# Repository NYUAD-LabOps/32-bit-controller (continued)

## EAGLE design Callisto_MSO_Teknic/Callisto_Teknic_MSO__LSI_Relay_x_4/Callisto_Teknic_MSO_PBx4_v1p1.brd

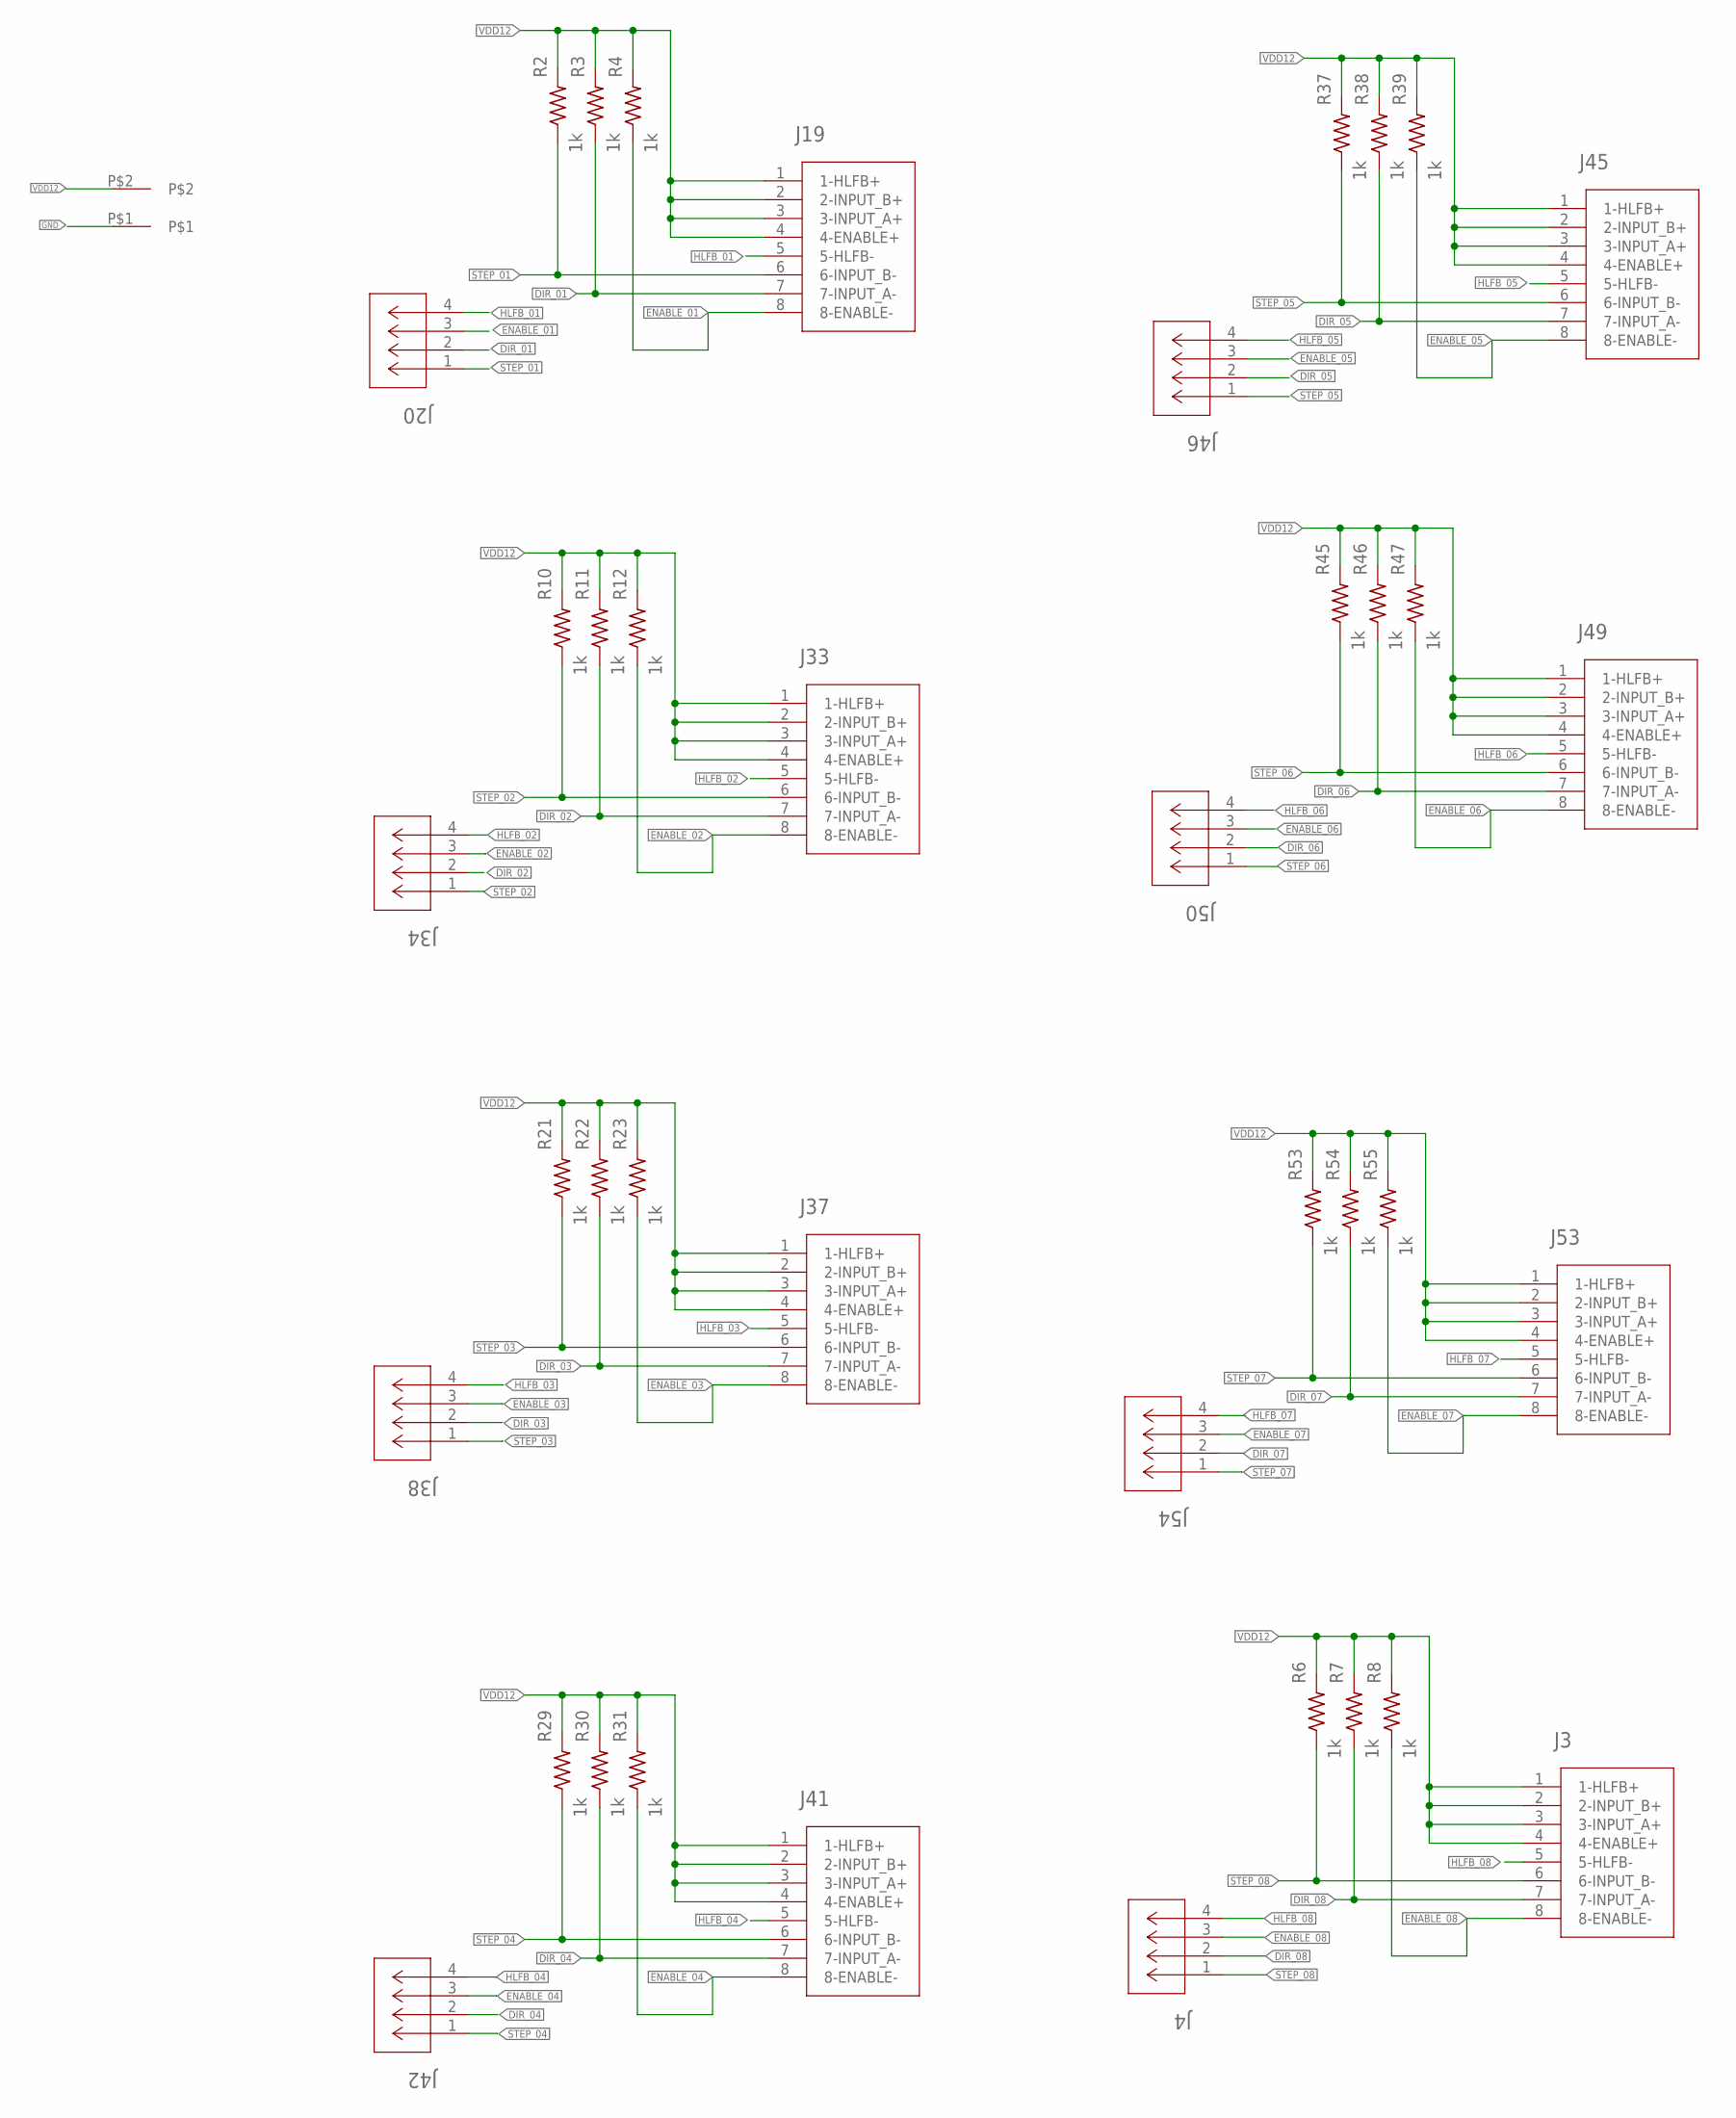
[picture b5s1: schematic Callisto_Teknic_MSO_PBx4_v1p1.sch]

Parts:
J2: 2-pos; 2_3.81MM_PITCH
J3, J19, J33, J37, J41, J45, J49, J53: TEKNIC_8PIN_MOTOR; CON_39281083
J4, J20, J34, J38, J42, J46, J50, J54: CONN_530470410_PICOBLADE_X_4; CON_530470410_MOL
R2, R3, R4, R6, R7, R8, R10, R11, R12, R21, R22, R23, R29, R30, R31, R37, R38, R39, R45, R46, R47, R53, R54, R55: 1k; 0805

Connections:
DIR_01: J19.7 (7-INPUT_A-), J20.2, R3.1
DIR_02: J33.7 (7-INPUT_A-), J34.2, R11.1
DIR_03: J37.7 (7-INPUT_A-), J38.2, R22.1
DIR_04: J41.7 (7-INPUT_A-), J42.2, R30.1
DIR_05: J45.7 (7-INPUT_A-), J46.2, R38.1
DIR_06: J49.7 (7-INPUT_A-), J50.2, R46.1
DIR_07: J53.7 (7-INPUT_A-), J54.2, R54.1
DIR_08: J3.7 (7-INPUT_A-), J4.2, R7.1
ENABLE_01: J19.8 (8-ENABLE-), J20.3, R4.1
ENABLE_02: J33.8 (8-ENABLE-), J34.3, R12.1
ENABLE_03: J37.8 (8-ENABLE-), J38.3, R23.1
ENABLE_04: J41.8 (8-ENABLE-), J42.3, R31.1
ENABLE_05: J45.8 (8-ENABLE-), J46.3, R39.1
ENABLE_06: J49.8 (8-ENABLE-), J50.3, R47.1
ENABLE_07: J53.8 (8-ENABLE-), J54.3, R55.1
ENABLE_08: J3.8 (8-ENABLE-), J4.3, R8.1
GND: J2.P$1
HLFB_01: J19.5 (5-HLFB-), J20.4
HLFB_02: J33.5 (5-HLFB-), J34.4
HLFB_03: J37.5 (5-HLFB-), J38.4
HLFB_04: J41.5 (5-HLFB-), J42.4
HLFB_05: J45.5 (5-HLFB-), J46.4
HLFB_06: J49.5 (5-HLFB-), J50.4
HLFB_07: J53.5 (5-HLFB-), J54.4
HLFB_08: J3.5 (5-HLFB-), J4.4
STEP_01: J19.6 (6-INPUT_B-), J20.1, R2.1
STEP_02: J33.6 (6-INPUT_B-), J34.1, R10.1
STEP_03: J37.6 (6-INPUT_B-), J38.1, R21.1
STEP_04: J41.6 (6-INPUT_B-), J42.1, R29.1
STEP_05: J45.6 (6-INPUT_B-), J46.1, R37.1
STEP_06: J49.6 (6-INPUT_B-), J50.1, R45.1
STEP_07: J53.6 (6-INPUT_B-), J54.1, R53.1
STEP_08: J3.6 (6-INPUT_B-), J4.1, R6.1
VDD12: J2.P$2, J3.1 (1-HLFB+), J3.2 (2-INPUT_B+), J3.3 (3-INPUT_A+), J3.4 (4-ENABLE+), J19.1 (1-HLFB+), J19.2 (2-INPUT_B+), J19.3 (3-INPUT_A+), J19.4 (4-ENABLE+), J33.1 (1-HLFB+), J33.2 (2-INPUT_B+), J33.3 (3-INPUT_A+), J33.4 (4-ENABLE+), J37.1 (1-HLFB+), J37.2 (2-INPUT_B+), J37.3 (3-INPUT_A+), J37.4 (4-ENABLE+), J41.1 (1-HLFB+), J41.2 (2-INPUT_B+), J41.3 (3-INPUT_A+), J41.4 (4-ENABLE+), J45.1 (1-HLFB+), J45.2 (2-INPUT_B+), J45.3 (3-INPUT_A+), J45.4 (4-ENABLE+), J49.1 (1-HLFB+), J49.2 (2-INPUT_B+), J49.3 (3-INPUT_A+), J49.4 (4-ENABLE+), J53.1 (1-HLFB+), J53.2 (2-INPUT_B+), J53.3 (3-INPUT_A+), J53.4 (4-ENABLE+), R2.2, R3.2, R4.2, R6.2, R7.2, R8.2, R10.2, R11.2, R12.2, R21.2, R22.2, R23.2, R29.2, R30.2, R31.2, R37.2, R38.2, R39.2, R45.2, R46.2, R47.2, R53.2, R54.2, R55.2

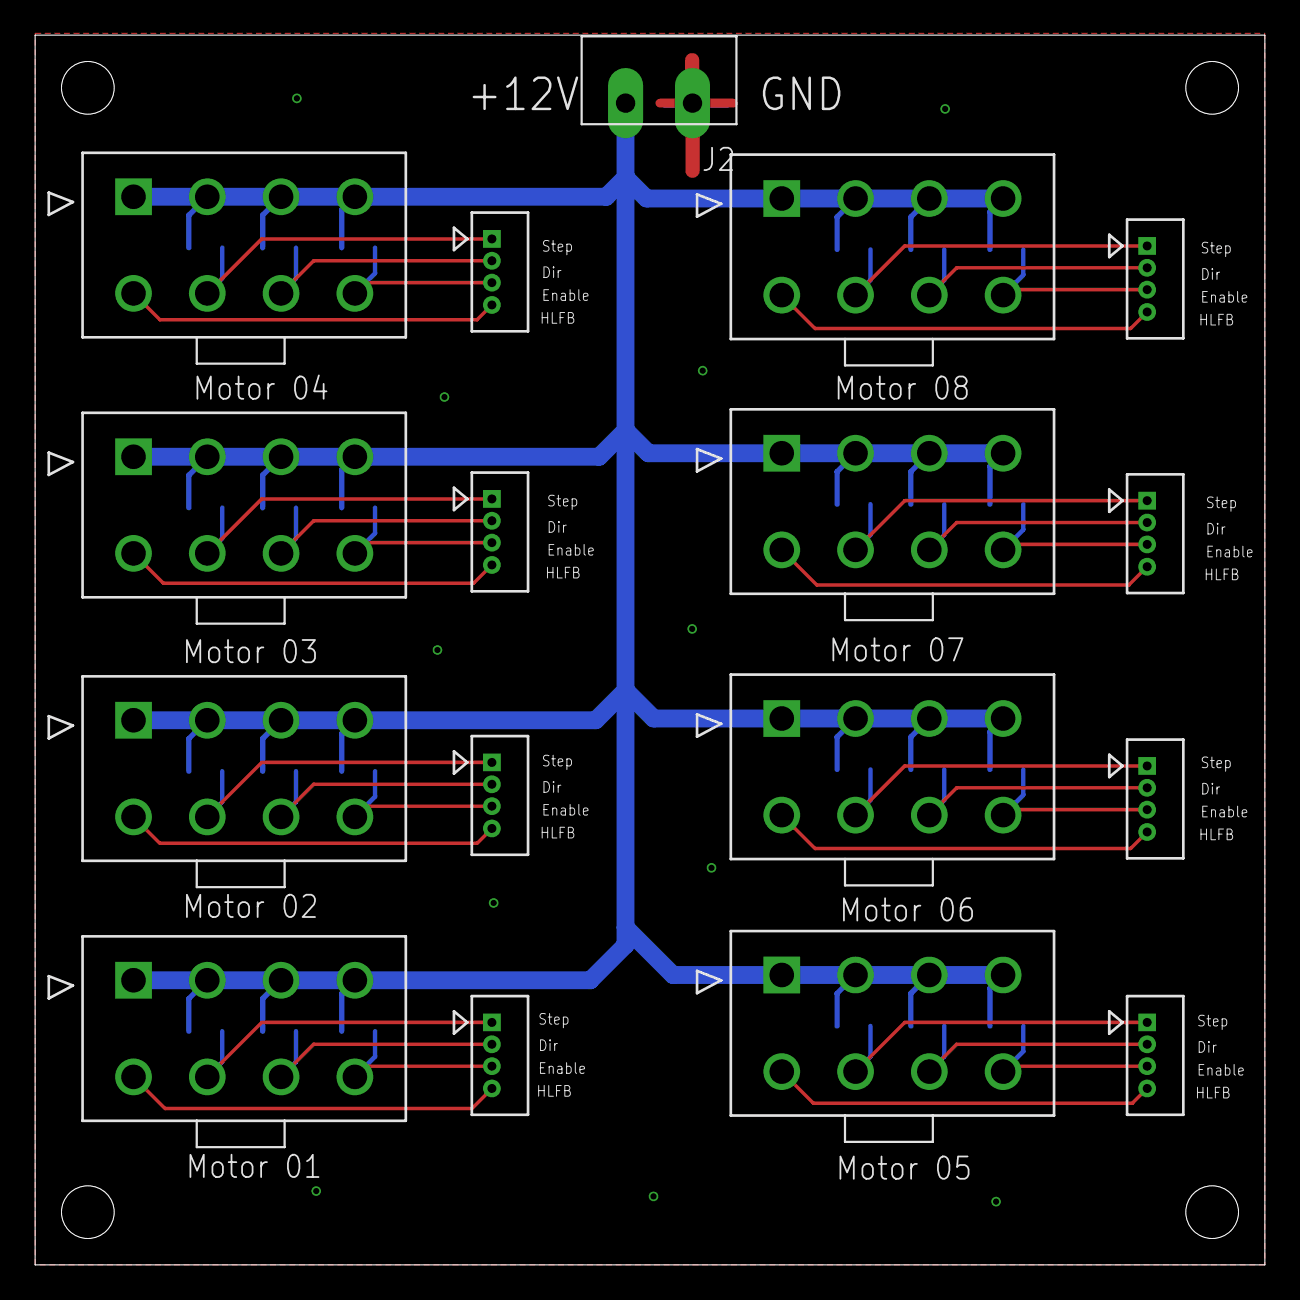
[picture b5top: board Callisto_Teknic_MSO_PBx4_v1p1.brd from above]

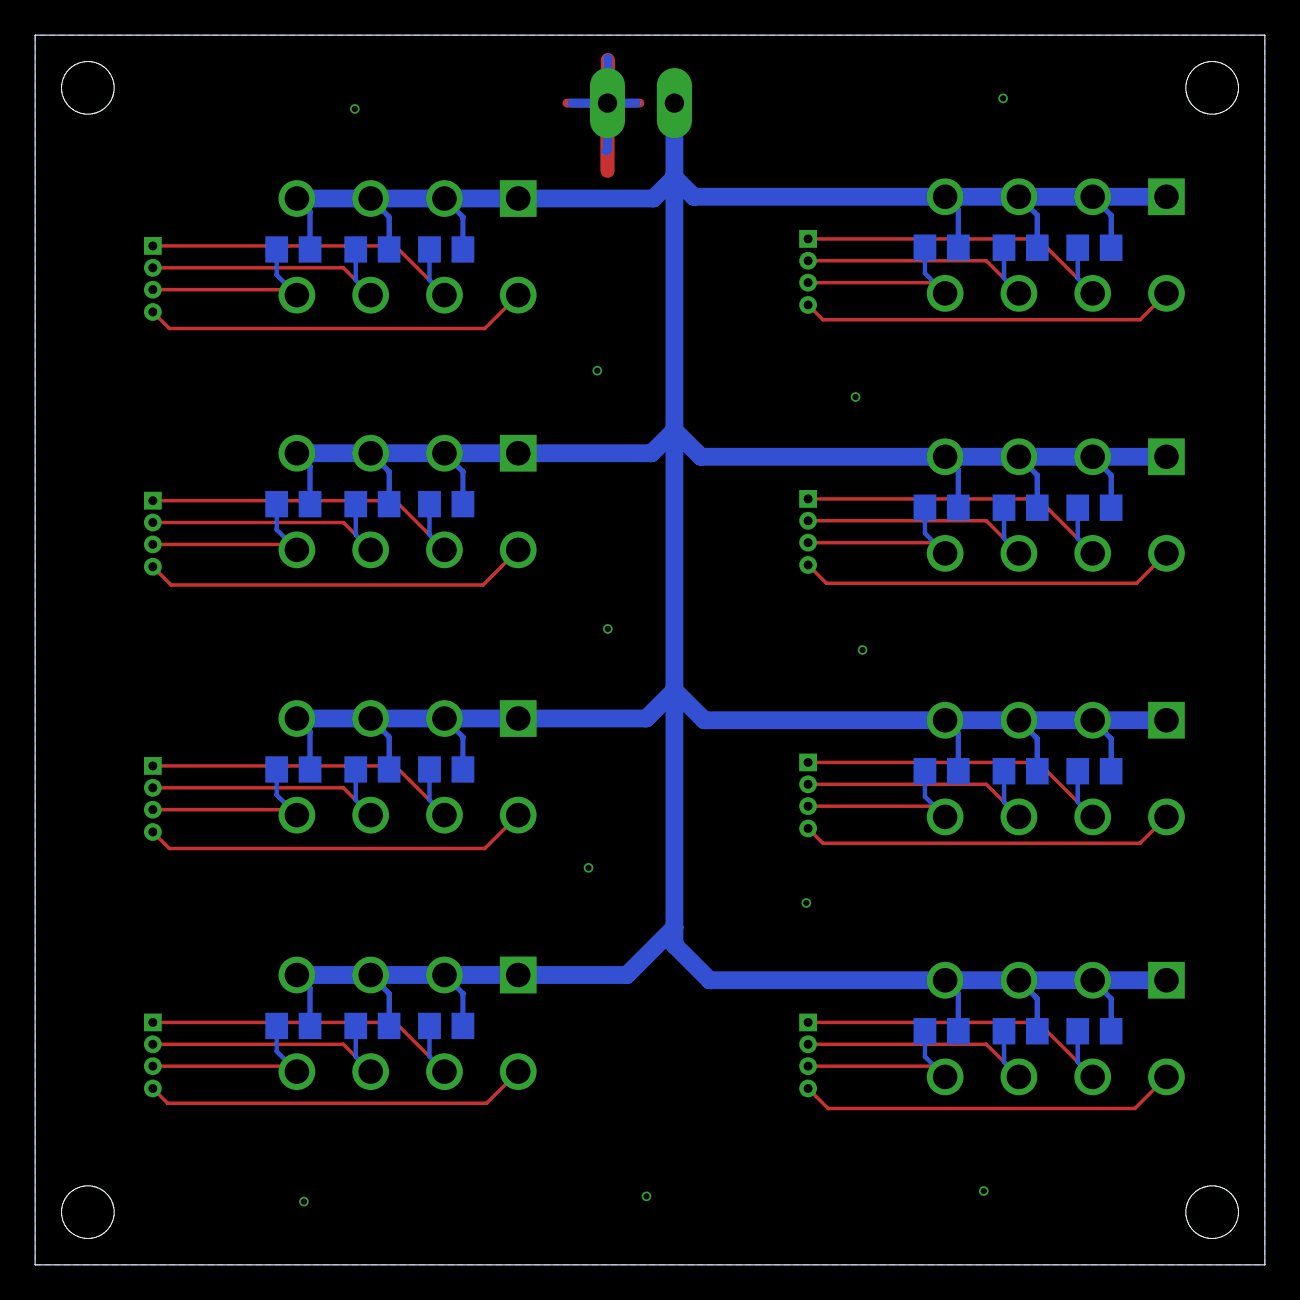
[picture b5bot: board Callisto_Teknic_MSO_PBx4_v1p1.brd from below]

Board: 2 copper layers, 70.0 x 70.0 mm, 41 parts (24 on the bottom side), 33 nets.
